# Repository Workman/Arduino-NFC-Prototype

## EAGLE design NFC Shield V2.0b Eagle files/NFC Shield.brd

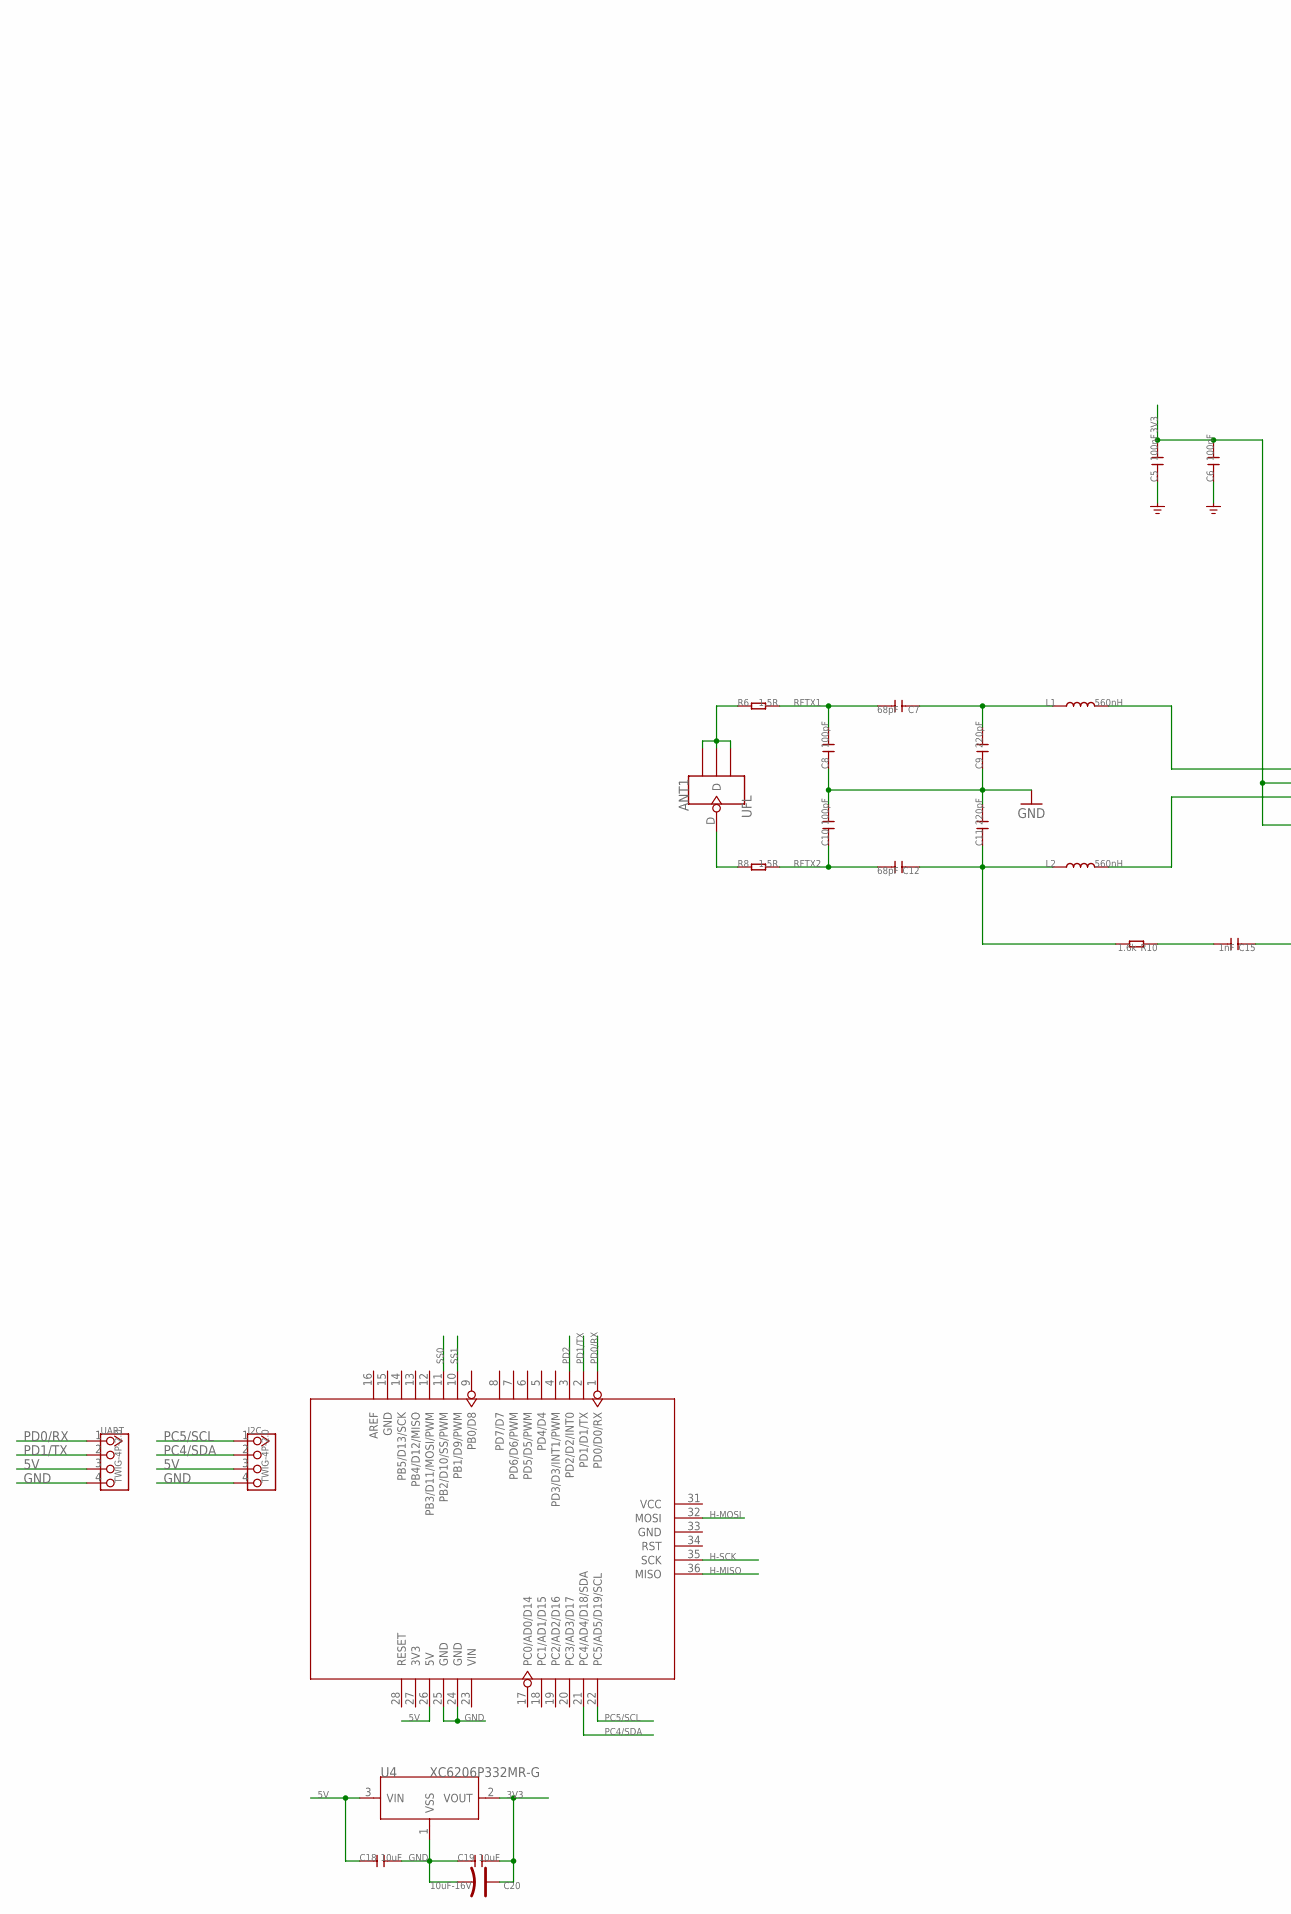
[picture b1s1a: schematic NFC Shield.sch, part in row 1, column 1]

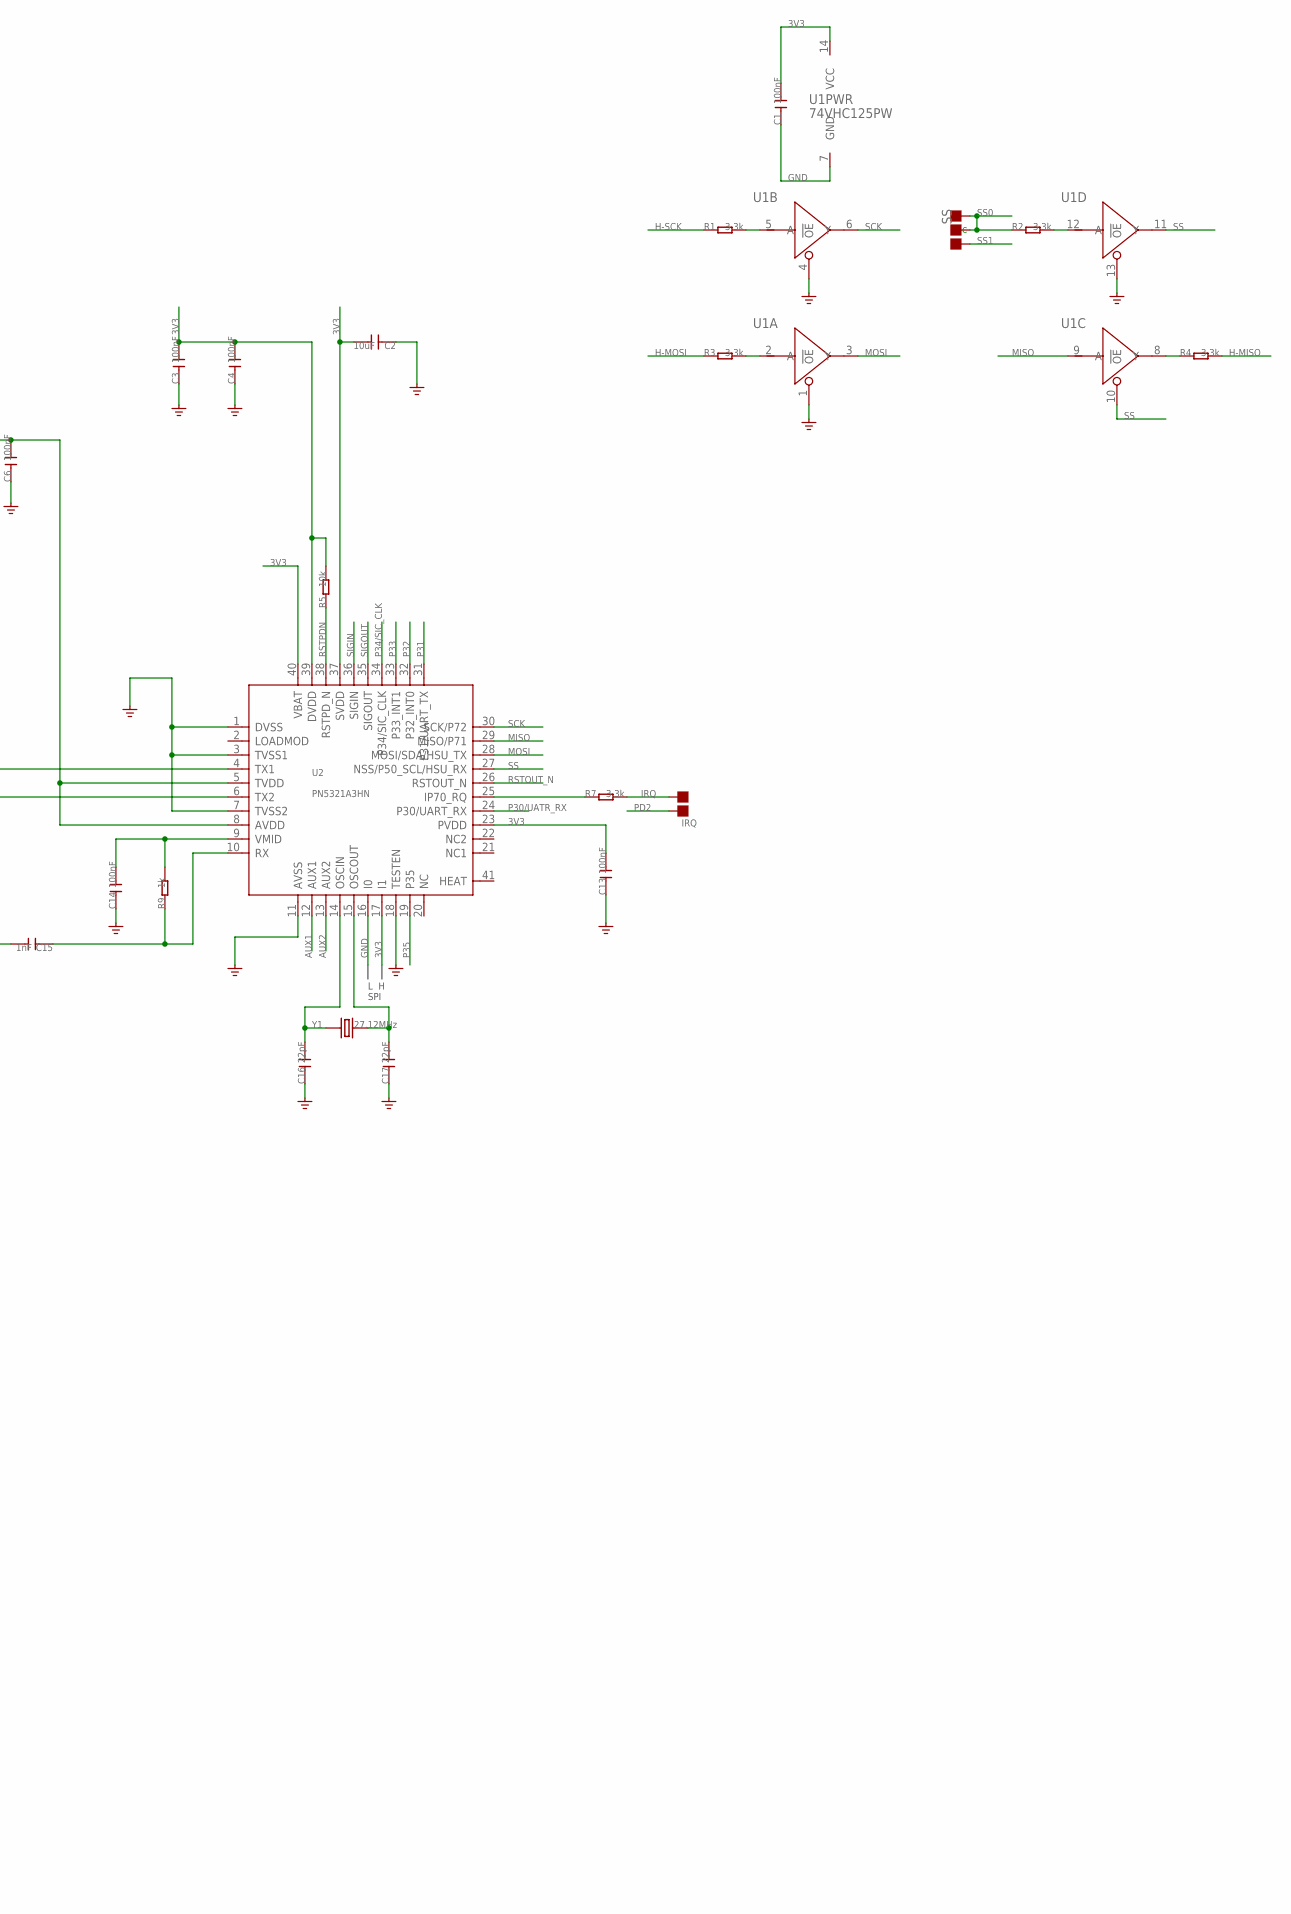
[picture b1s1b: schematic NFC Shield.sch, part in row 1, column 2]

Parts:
ANT1: UFL; 4P-U-FL
C1, C3, C4, C5, C6, C13, C14: 100nF; C0603
C2: 10uF; 0805
C7, C12: 68pF; C0603
C8, C10: 100pF; C0603
C9, C11: 220pF; C0603
C15: 1nF; C0603
C16, C17: 22pF; C0603
C18, C19: 10uF; C0805
C20: 10uF-16V; AVX-A
I2C: TWIG-4P-2.0; 4P-2.0
IRQ: DNP; 2P-SMD-1.78X1.27
L1, L2: 560nH; L0805
R1, R2, R3, R4, R7: 3.3k; R0603
R5: 10k; R0603
R6, R8: 1.5R; R0603
R9: 1k; R0603
R10: 1.6k; R0603
SS: DNP; 3P-SMD-4.1X1.5
U1: 74VHC125PW; TSSOP14
U2: PN5321A3HN; HVQFN40
U3: ARDUINO'W/-SILK; ARDUINO
U4: XC6206P332MR-G; SOT23
UART: TWIG-4P-2.0; 4P-2.0
Y1: 27.12MHz; HC49/S

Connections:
3V3: C1.2, C2.2, C3.2, C4.2, C5.2, C6.2, C13.2, C19.2, C20.+, R5.2, U1.14 (VCC), U2.5 (TVDD), U2.8 (AVDD), U2.17 (I1), U2.23 (PVDD), U2.37 (SVDD), U2.39 (DVDD), U2.40 (VBAT), U4.2 (VOUT)
5V: C18.1, I2C.3, U3.26 (5V), U4.3 (VIN), UART.3
AUX1: U2.12 (AUX1)
AUX2: U2.13 (AUX2)
GND: C1.1, C2.1, C3.1, C4.1, C5.1, C6.1, C8.1, C9.1, C10.2, C11.2, C13.1, C14.1, C16.1, C17.1, C18.2, C19.1, C20.-, I2C.4, U1.1 (!OE), U1.4 (!OE), U1.7 (GND), U1.13 (!OE), U2.1 (DVSS), U2.3 (TVSS1), U2.7 (TVSS2), U2.11 (AVSS), U2.16 (I0), U2.18 (TESTEN), U3.24 (GND), U3.25 (GND), U4.1 (VSS), UART.4
H-MISO: R4.2, U3.36 (MISO)
H-MOSI: R3.1, U3.32 (MOSI)
H-SCK: R1.1, U3.35 (SCK)
IRQ: IRQ.1, R7.2
MISO: U1.9 (A), U2.29 (MISO/P71)
MOSI: U1.3 (Y), U2.28 (MOSI/SDA/HSU_TX)
unnamed: C16.2, U2.14 (OSCIN), Y1.1
unnamed: C17.2, U2.15 (OSCOUT), Y1.2
unnamed: L2.2, U2.6 (TX2)
unnamed: L1.2, U2.4 (TX1)
unnamed: C7.1, C9.2, L1.1
unnamed: C15.2, R10.1
unnamed: C11.1, C12.1, L2.1, R10.2
unnamed: R1.2, U1.5 (A)
unnamed: C14.2, R9.2, U2.9 (VMID)
unnamed: R2.2, U1.12 (A)
unnamed: C15.1, R9.1, U2.10 (RX)
unnamed: R4.1, U1.8 (Y)
unnamed: R3.2, U1.2 (A)
unnamed: R7.1, U2.25 (IP70_RQ)
unnamed: ANT1.D, R8.1
unnamed: ANT1.GND1, ANT1.GND2, ANT1.GND3, R6.1
P30/UATR_RX: U2.24 (P30/UART_RX)
P31: U2.31 (P31/UART_TX)
P32: U2.32 (P32_INT0)
P33: U2.33 (P33_INT1)
P34/SIC_CLK: U2.34 (P34/SIC_CLK)
P35: U2.19 (P35)
PC4/SDA: I2C.2, U3.21 (PC4/AD4/D18/SDA)
PC5/SCL: I2C.1, U3.22 (PC5/AD5/D19/SCL)
PD0/RX: U3.1 (PD0/D0/RX), UART.1
PD1/TX: U3.2 (PD1/D1/TX), UART.2
PD2: IRQ.2, U3.3 (PD2/D2/INT0)
RFTX1: C7.2, C8.2, R6.2
RFTX2: C10.1, C12.2, R8.2
RSTOUT_N: U2.26 (RSTOUT_N)
RSTPDN: R5.1, U2.38 (RSTPD_N)
SCK: U1.6 (Y), U2.30 (SCK/P72)
SIGIN: U2.36 (SIGIN)
SIGOUT: U2.35 (SIGOUT)
SS: U1.10 (!OE), U1.11 (Y), U2.27 (NSS/P50_SCL/HSU_RX)
SS0: R2.1, SS.11 (R), SS.MM (C), U3.11 (PB2/D10/SS/PWM)
SS1: SS.00 (L), U3.10 (PB1/D9/PWM)

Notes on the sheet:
SPI

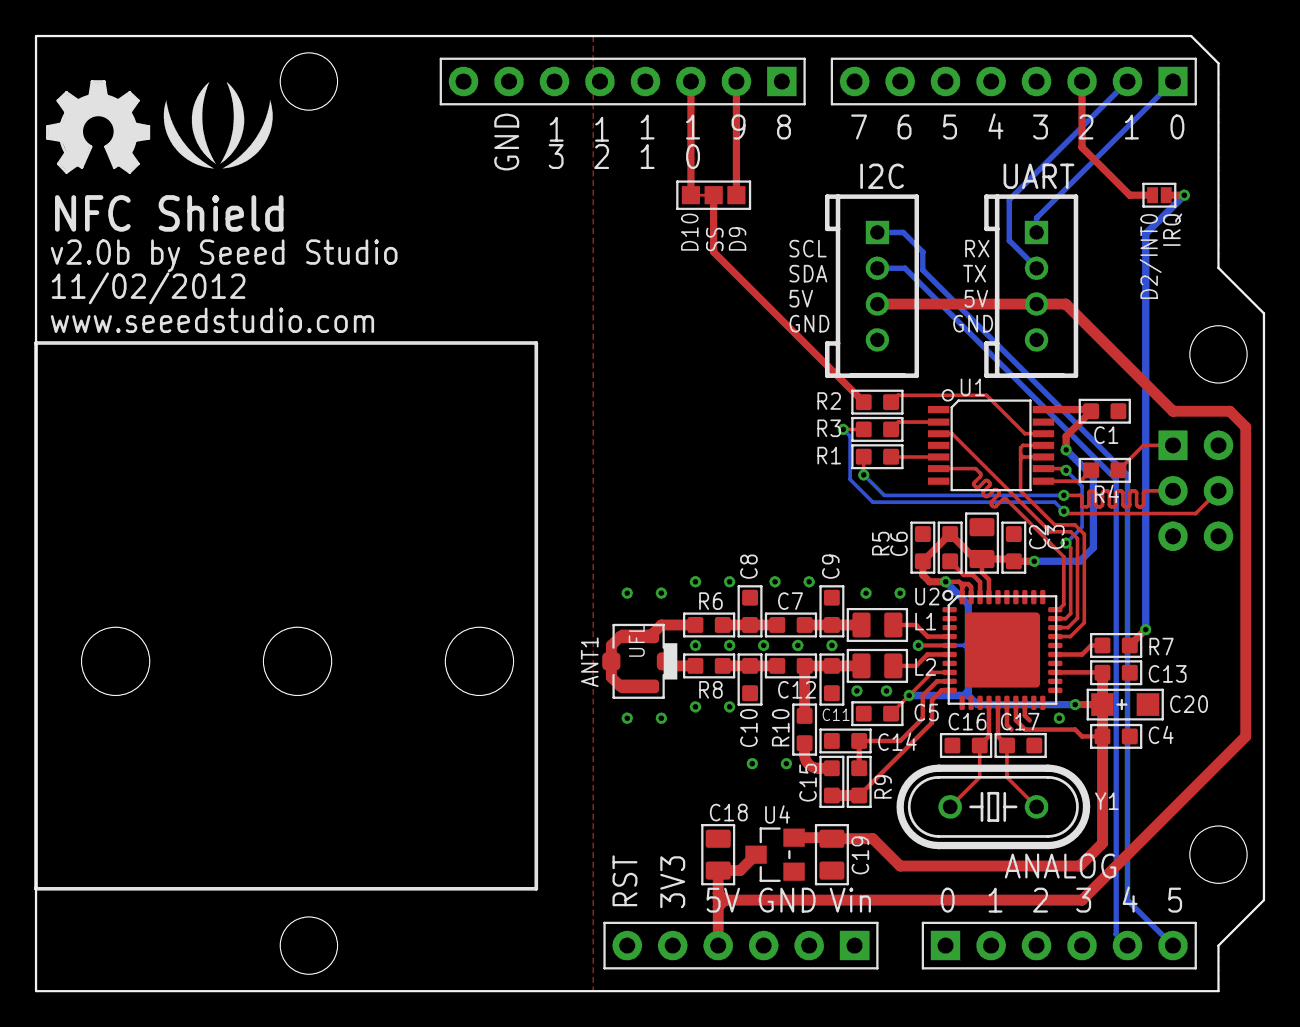
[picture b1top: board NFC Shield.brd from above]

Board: 2 copper layers, 68.6 x 53.3 mm, 44 parts (0 on the bottom side), 37 nets.

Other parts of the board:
U$1: OSHW_FILLX200_NOTEXT
U$2: LOGO_SILK

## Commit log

2013-06-02 Unspecified updates
2013-09-09 Successfully 'popped' a request =]
2013-09-09 Cleaned up requests and received data.
2013-09-09 More cleanup
2013-09-14 Successfully sending requests
2013-10-11 Don't scan networks. Set local band. Added specific tag support.
2013-10-11 Updated sender data
